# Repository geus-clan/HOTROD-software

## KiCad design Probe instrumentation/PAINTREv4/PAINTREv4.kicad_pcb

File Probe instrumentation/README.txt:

This folder contains the project files for the internal instrumentation of PAINTREv3.
The schematic and PCB layout (KiCad format), as well as gerber files for production, are included in the folder PAINTREv3.
The software for PAINTREv3 is included in the PAINTRE_V3XR folder. Various legacy versions featuring different methods are included, though the main PAINTRE_V3XR version is the recommended release, field-tested and confirmed functional.
Due to complications with the atmega328p processors used in assembly, our field versions of PAINTRE were retrofitted with Teensy-LC microprocessors. The connections to power and i2c lines are apparent in the setup of the software. Additional questions can be emailed to clan at geus.dk.

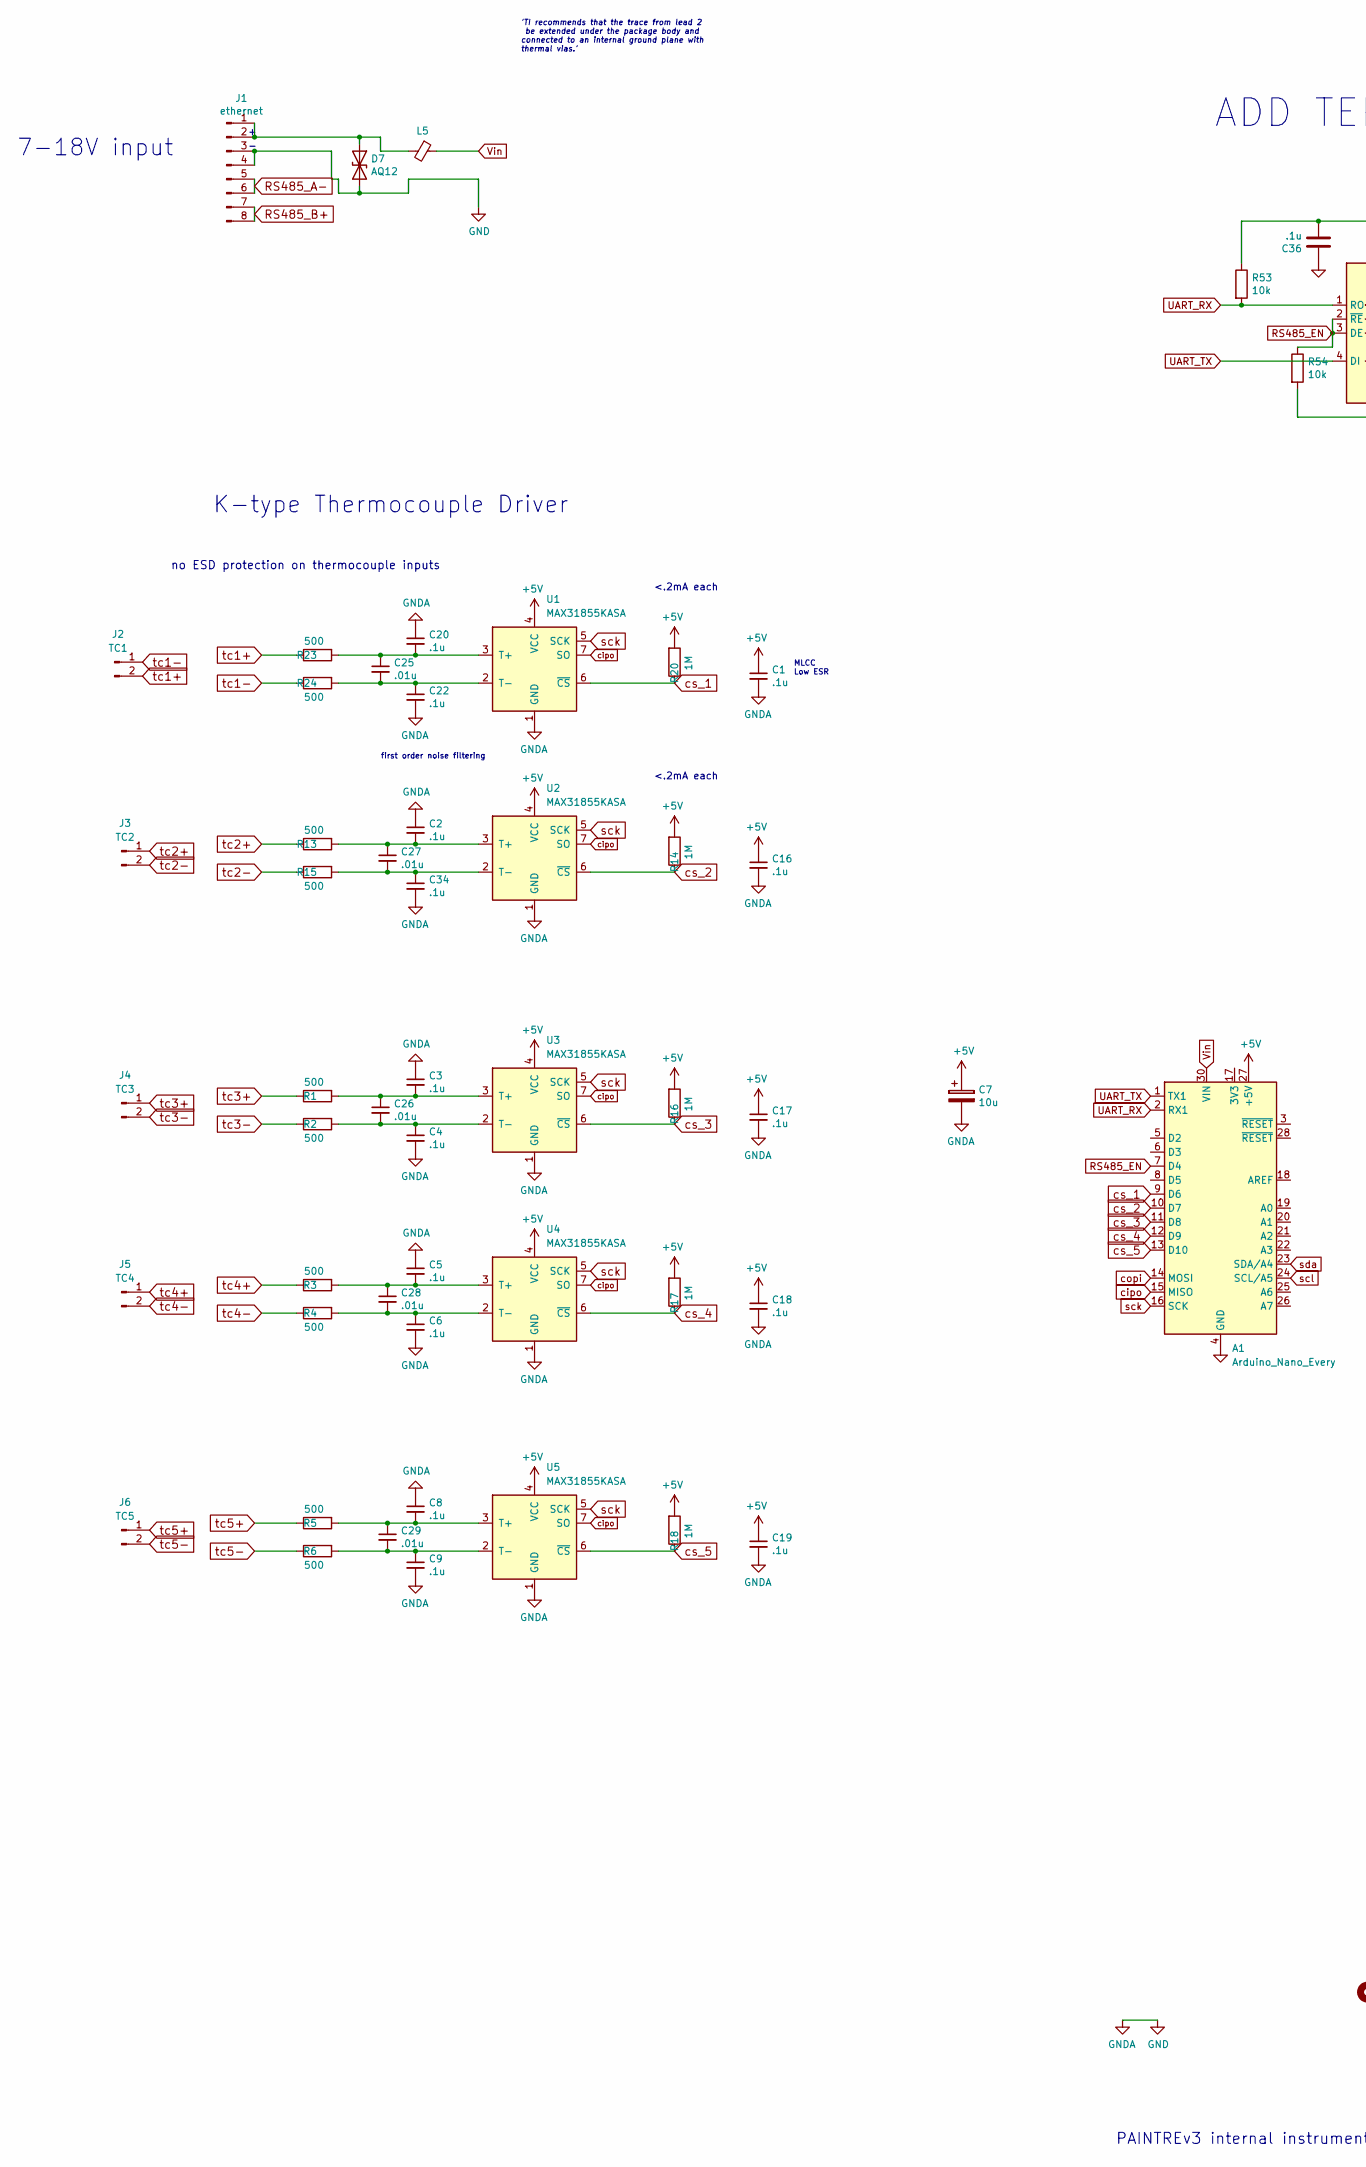
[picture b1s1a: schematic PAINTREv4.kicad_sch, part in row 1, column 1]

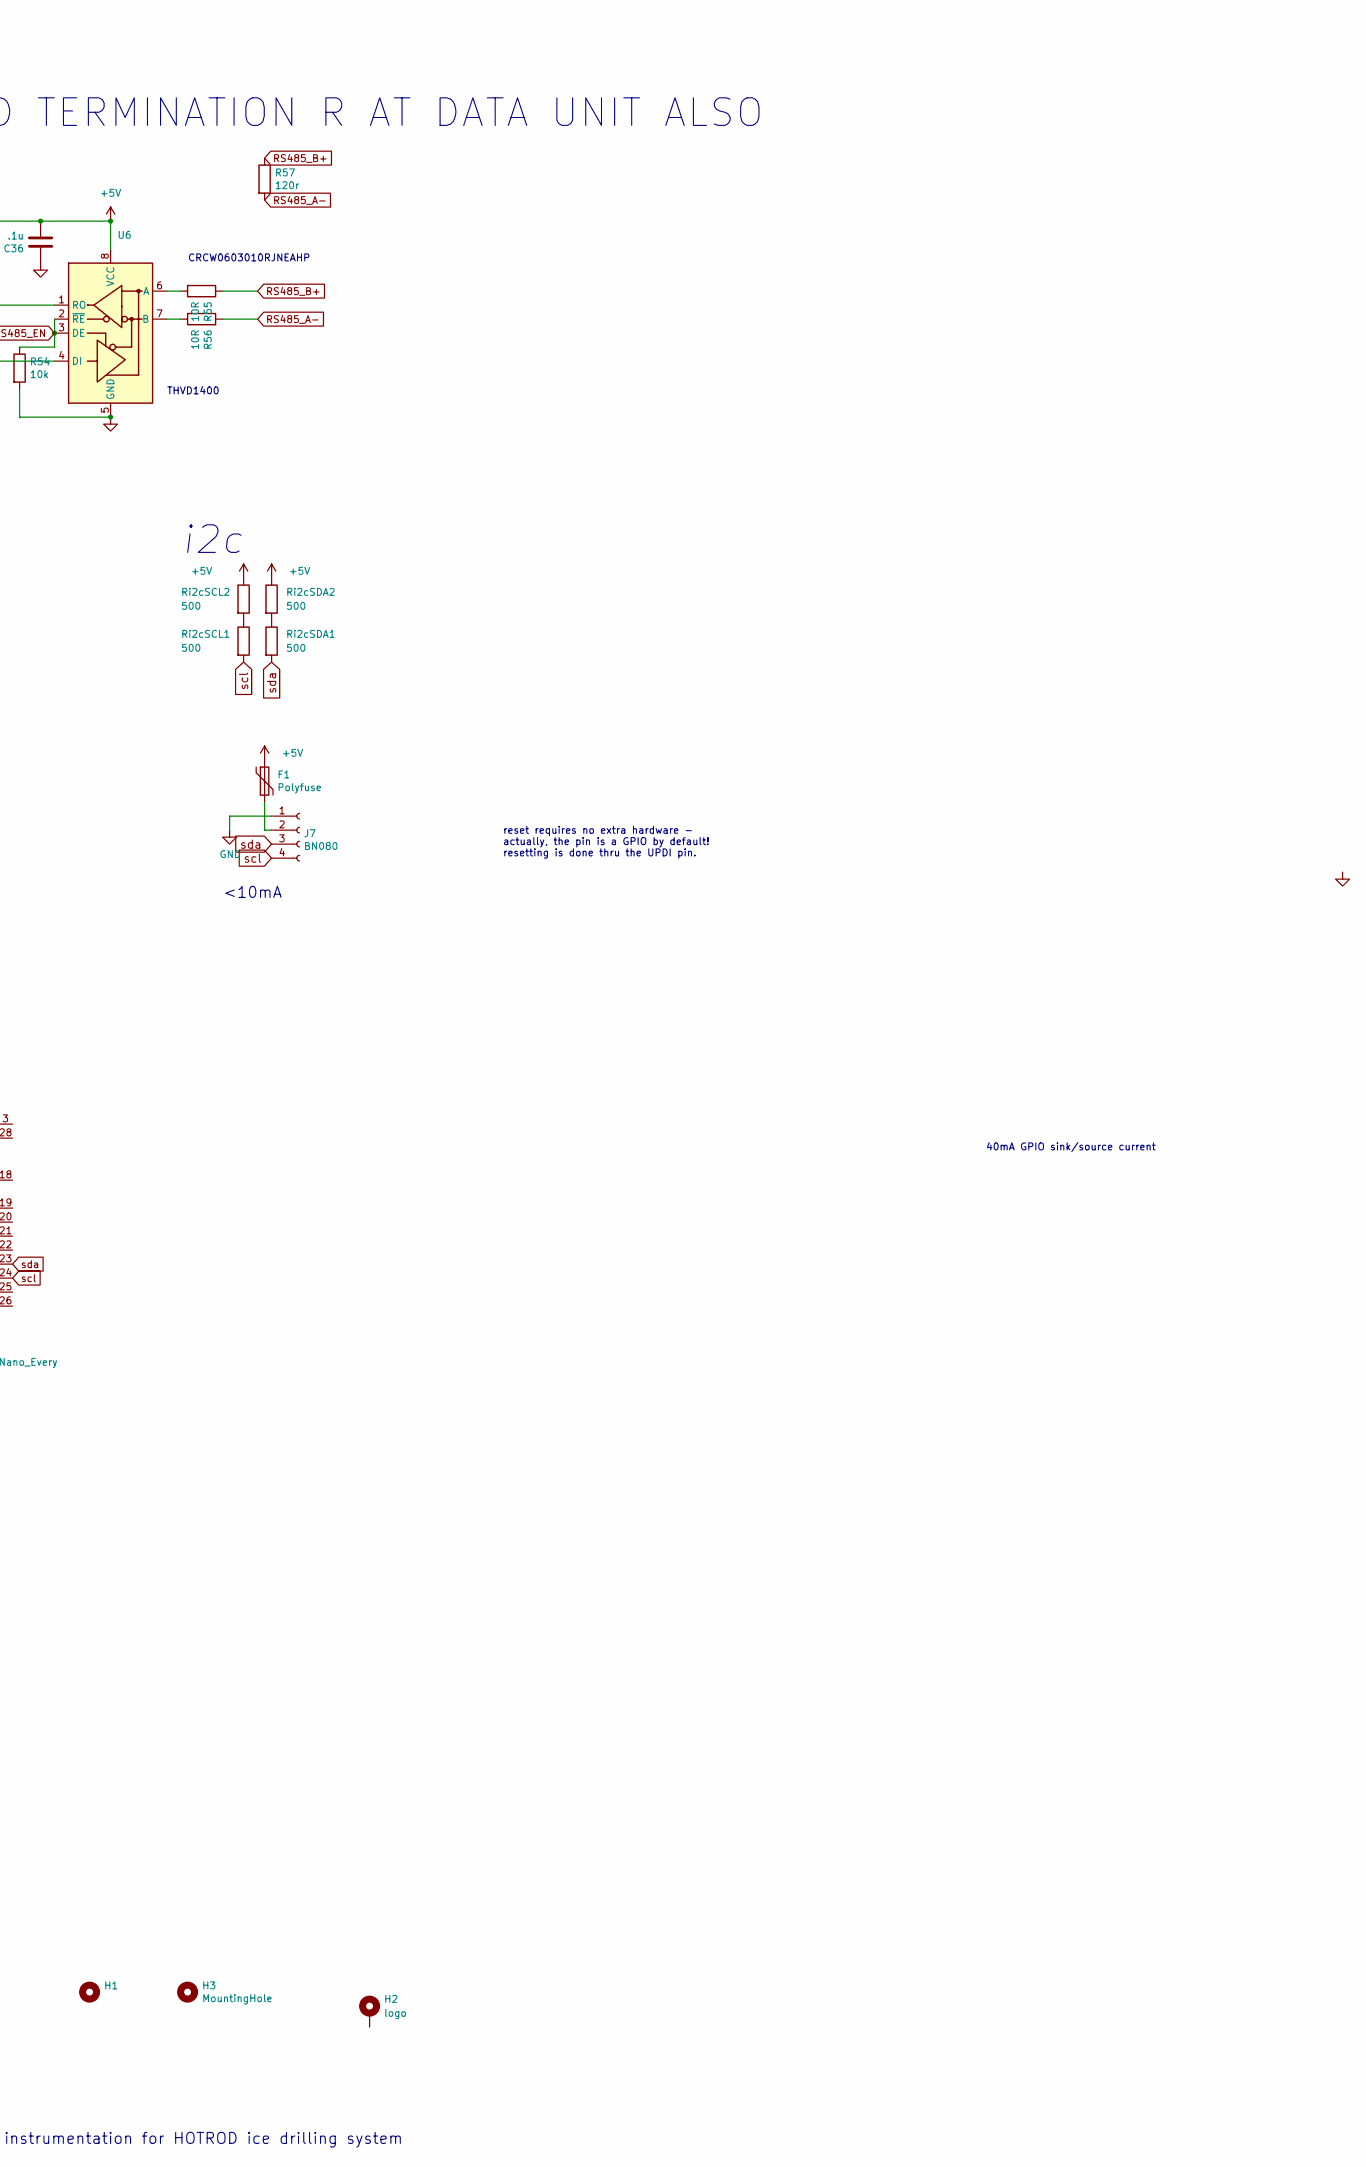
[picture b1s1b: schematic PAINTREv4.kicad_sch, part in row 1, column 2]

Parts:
A1: Arduino_Nano_Every; Arduino_Nano
C1, C2, C3, C4, C5, C6, C8, C9, C16, C17, C18, C19, C20, C22, C34: .1u; C_0603_1608Metric_fabdesignatorsmall
C7: 10u; C_1206_HandSoldering_silkscreenlabel
C25, C26, C27, C28, C29: .01u; C_0603_1608Metric_fabdesignatorsmall
C36: .1u; C_0603_1608Metric_fabdesignatorsmall; JLC part number C1525
D7: AQ12; SOT-23_handsoldering
F1: Polyfuse; Fuse_0603_1608Metric
H1: MountingHole_3.2mm_M3
H2: logo; paintre v4 logo
H3: MountingHole; MountingHole_3.2mm_M3
J1: ethernet; PinSocket_1x08_P2.00mm_Vertical
J2: TC1; PinSocket_1x02_P2.54mm_Vertical
J3: TC2; PinSocket_1x02_P2.54mm_Vertical
J4: TC3; PinSocket_1x02_P2.54mm_Vertical
J5: TC4; PinSocket_1x02_P2.54mm_Vertical
J6: TC5; PinSocket_1x02_P2.54mm_Vertical
J7: BN080; JST_SH_SM04B-SRSS-TB_04x1.00mm_Angled
L5: Ferrite_Bead_Small; ferrite_bead_1206
R1, R2, R3, R4, R5, R6, R13, R15, R23, R24: 500; R_0603_1608Metric_fabdesignatorsmall
R14, R16, R17, R18, R20: 1M; R_0603_1608Metric_fabdesignatorsmall
R53, R54: 10k; R_0603_1608Metric_fabdesignatorsmall; JLC part number C17903
R55, R56: 10R; R_0603_1608Metric_fabdesignatorsmall; JLC part number C17903
R57: 120r; R_1210_3225Metric_Pad1.30x2.65mm_HandSolder; JLC part number ---
Ri2cSCL1, Ri2cSCL2, Ri2cSDA1, Ri2cSDA2: 500; R_0603_1608Metric_fabdesignatorsmall
U1, U2, U3, U4, U5: MAX31855KASA; SOIC-8_3.9x4.9mm_P1.27mm
U6: SOT-5X3-8

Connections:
+5V: A1.27 (+5V), C1.1, C7.1, C16.1, C17.1, C18.1, C19.1, C36.2, F1.1, R14.2, R16.2, R17.2, R18.2, R20.2, R53.1, Ri2cSCL2.1, Ri2cSDA2.1, U1.4 (VCC), U2.4 (VCC), U3.4 (VCC), U4.4 (VCC), U5.4 (VCC), U6.8 (VCC)
unnamed: C2.2, C27.1, R13.2, U2.3 (T+)
unnamed: C20.2, C25.1, R23.2, U1.3 (T+)
unnamed: C22.1, C25.2, R24.2, U1.2 (T-)
unnamed: C3.2, C26.1, R1.2, U3.3 (T+)
unnamed: C4.1, C26.2, R2.2, U3.2 (T-)
unnamed: C27.2, C34.1, R15.2, U2.2 (T-)
unnamed: C5.2, C28.1, R3.2, U4.3 (T+)
unnamed: C6.1, C28.2, R4.2, U4.2 (T-)
unnamed: C8.2, C29.1, R5.2, U5.3 (T+)
unnamed: C9.1, C29.2, R6.2, U5.2 (T-)
unnamed: D7.1 (A1), J1.1, J1.2, L5.2
unnamed: F1.2, J7.2
unnamed: R55.2, U6.6 (A)
unnamed: R56.2, U6.7 (B)
unnamed: Ri2cSCL1.1, Ri2cSCL2.2
unnamed: Ri2cSDA1.1, Ri2cSDA2.2
RS485_A-: J1.5, J1.6, R56.1, R57.2
RS485_B+: J1.7, J1.8, R55.1, R57.1
RS485_EN: A1.7 (D4), R54.1, U6.2 (~RE), U6.3 (DE)
UART_RX: A1.2 (RX1), R53.2, U6.1 (RO)
UART_TX: A1.1 (TX1), U6.4 (DI)
Vin: A1.30 (VIN), L5.1
cipo: A1.15 (MISO), U1.7 (SO), U2.7 (SO), U3.7 (SO), U4.7 (SO), U5.7 (SO)
copi: A1.14 (MOSI)
cs_1: A1.9 (D6), R20.1, U1.6 (~CS)
cs_2: A1.10 (D7), R14.1, U2.6 (~CS)
cs_3: A1.11 (D8), R16.1, U3.6 (~CS)
cs_4: A1.12 (D9), R17.1, U4.6 (~CS)
cs_5: A1.13 (D10), R18.1, U5.6 (~CS)
sck: A1.16 (SCK), U1.5 (SCK), U2.5 (SCK), U3.5 (SCK), U4.5 (SCK), U5.5 (SCK)
scl: A1.24 (SCL/A5), J7.4, Ri2cSCL1.2
sda: A1.23 (SDA/A4), J7.3, Ri2cSDA1.2
tc1+: J2.2, R23.1
tc1-: J2.1, R24.1
tc2+: J3.1, R13.1
tc2-: J3.2, R15.1
tc3+: J4.1, R1.1
tc3-: J4.2, R2.1
tc4+: J5.1, R3.1
tc4-: J5.2, R4.1
tc5+: J6.1, R5.1
tc5-: J6.2, R6.1

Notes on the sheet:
<.2mA each
CRCW0603010RJNEAHP
MLCC Low ESR
first order noise filtering
reset requires no extra hardware - actually, the pin is a GPIO by default! resetting is done thru the UPDI pin.
THVD1400
40mA GPIO sink/source current
ADD TERMINATION R AT DATA UNIT ALSO
7-18V input
K-type Thermocouple Driver
PAINTREv3 internal instrumentation for HOTROD ice drilling system
<10mA
no ESD protection on thermocouple inputs
'TI recommends that the trace from lead 2 be extended under the package body and connected to an internal ground plane with thermal vias.'
i2c

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
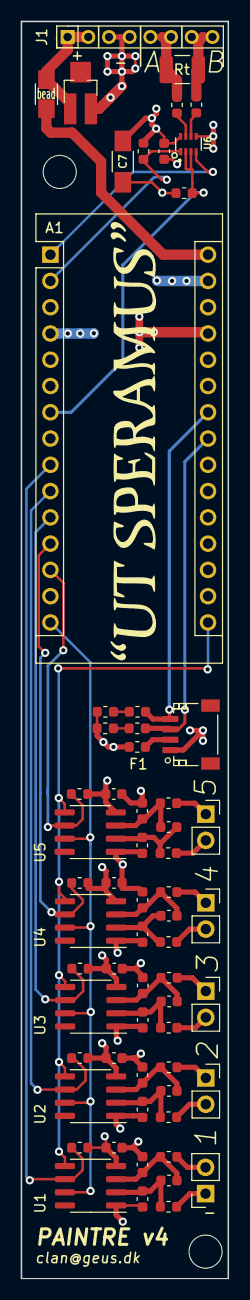
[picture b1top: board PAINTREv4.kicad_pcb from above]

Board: 4 copper layers, 20.0 x 121.5 mm, 66 parts (0 on the bottom side), 43 nets.

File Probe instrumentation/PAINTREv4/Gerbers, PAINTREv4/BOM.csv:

Designator,Package,Quantity,Value,JLC,SKU,MPN,LINK
"C1, C2, C3, C4, C5, C6, C8, C9, C16, C17, C18, C19, C20, C22, C34, C36",603,16,.1u,,302010139,CC0603KRX7R8BB105,
"C25, C26, C27, C28, C29",603,5,.01u,,302010138,CC0603KRX7R9BB104,
"R1, R2, R3, R4, R5, R6, R13, R15, R23, R24, Ri2cSCL1, Ri2cSCL2, Ri2cSDA1, Ri2cSDA2",603,14,500R,,301010157,RC0603JR-07510RL,
"R14, R16, R17, R18, R20",603,5,1M,,301010100,RC0603JR-071ML,
"R53, R54",603,2,10k,C25804,,,
"R55, R56",603,2,10R 330mW,,,CRCW060310R0JNEAHP,https://www.mouser.dk/ProductDetail/Vishay-Dale/CRCW060310R0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
F1,603,1,Polyfuse,,,0ZCM0002FF2G,https://www.mouser.dk/ProductDetail/Bel-Fuse/0ZCM0002FF2G/?q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
"U1, U2, U3, U4, U5",SOIC-8_3.9x4.9mm_P1.27mm,5,MAX31855KASA,,,MAX31855KASA+T,https://www.mouser.dk/ProductDetail/Maxim-Integrated/MAX3185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
U6,SOT-5X3-8,1,THVD1400,,,THVD1400DRLR,https://www.mouser.dk/ProductDetail/Texas-Instruments/THVD14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
D7,SOT-23,1,AQ12,,,,
J7,JST_SH_SM04B-SRSS-TB_04x1.00mm_Angled,1,BN080,,,PRT-14417,https://www.mouser.dk/ProductDetail/SparkFun/PRT-14417?qs=sG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

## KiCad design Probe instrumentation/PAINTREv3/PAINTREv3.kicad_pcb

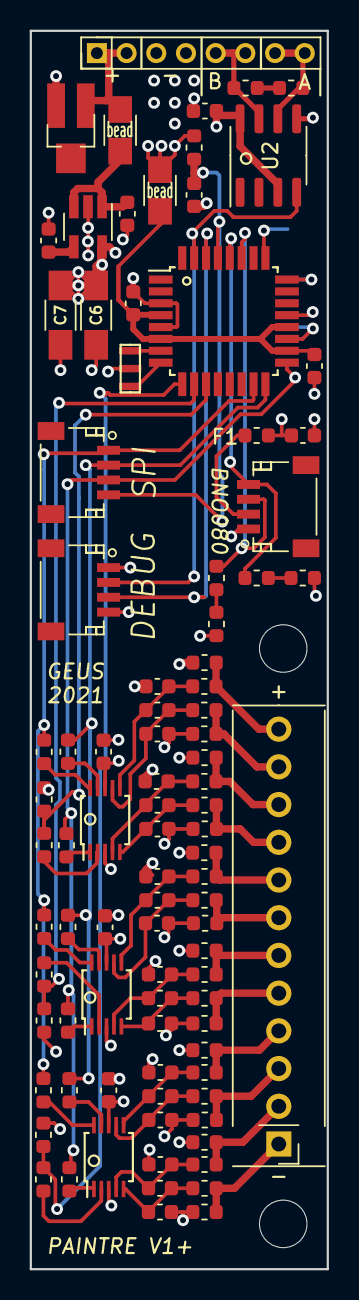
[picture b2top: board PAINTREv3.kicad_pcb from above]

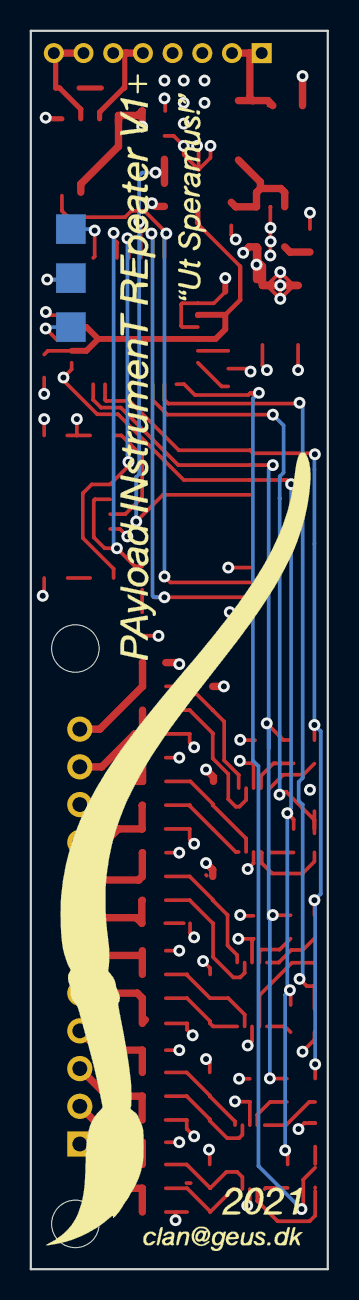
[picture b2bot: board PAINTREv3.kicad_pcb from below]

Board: 4 copper layers, 20.0 x 83.4 mm, 97 parts (3 on the bottom side), 64 nets.

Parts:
C1, C2, C4, C9, C11, C12, C14, C17, C18, C19, C20, C22, C23, C26, C27, C28, C29, C30: .1u; C_0603_1608Metric_fabdesignatorsmall
C3, C8, C10, C13, C15, C16, C21, C24, C25: 1u; C_0603_1608Metric_fabdesignatorsmall
C5: 10n; C_0603_1608Metric_fabdesignatorsmall
C6, C7: 10u; C_1206_HandSoldering_silkscreenlabel
D7: AQ12; SOT-23_handsoldering
F1: Polyfuse; Fuse_0603_1608Metric
H1, H2: MountingHole; MountingHole_3.2mm_M3
J1: ethernet; PinSocket_1x08_P2.00mm_Vertical
J2: SPI; JST_SH_SM04B-SRSS-TB_04x1.00mm_Angled
J3: TC; ScrewTerminal_1x12_P2.54mm_Vertical
J5: debug; JST_SH_SM04B-SRSS-TB_04x1.00mm_Angled
J7: BN080; JST_SH_SM04B-SRSS-TB_04x1.00mm_Angled
L5, L6: Ferrite_Bead_Small; ferrite_bead_1206
R1, R2, R3, R4, R12, R16, R20, R22, R25, R27, R28, R29, R30, R31, R40: 1M; R_0603_1608Metric_fabdesignatorsmall
R5, R6, R7, R8, R13, R15, R23, R24, R32, R33, R34, R35: 500; R_0603_1608Metric_fabdesignatorsmall
R9, R10, R11, R17, R18, R19, R21, R26, R36, R37, R38, R39: 50; R_0603_1608Metric_fabdesignatorsmall
R14: 4.7k; R_0603_1608Metric_fabdesignatorsmall
Ri2cSCL1, Ri2cSCL2, Ri2cSDA1, Ri2cSDA2: 500; R_0603_1608Metric_fabdesignatorsmall
Rterm1, Rterm2: 50; R_0603_1608Metric_fabdesignatorsmall
TP2: pc0; TestPoint_Pad_2.0x2.0mm
TP3: pc1; TestPoint_Pad_2.0x2.0mm
TP4: pc2; TestPoint_Pad_2.0x2.0mm
U1: LP2985-3.3; SOT-23-5_HandSoldering
U2: THVD1428DR; SOIC-8_3.9x4.9mm_P1.27mm
U3, U4, U7: ADS1118IDGS; TSSOP-10_3x3mm_P0.5mm
U5: ATmega328P-AU; TQFP-32_7x7mm_Pitch0.8mm
Y1: 8MHz Resonator; Resonator_SMD_muRata_CSTNE

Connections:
+3V3: C1.1, C6.1, C7.1, C9.1, C12.1, C23.1, C30.1, F1.1, J5.1, L6.1, R1.1, R3.1, R12.1, R14.1, R20.2, R22.1, R27.2, R28.1, R30.1, R40.2, Ri2cSCL2.1, Ri2cSDA2.1, U1.5, U2.3, U2.8, U3.8, U4.8, U7.8
GND: C1.2, C2.1, C4.2, C5.2, C6.2, C7.2, C9.2, C11.1, C12.2, C13.2, C14.2, C15.2, C16.2, C17.2, C18.1, C19.2, C20.1, C22.2, C23.2, C26.1, C27.2, C28.1, C29.2, C30.2, D7.2, J1.3, J1.4, J5.4, J7.1, R2.2, R4.2, R16.2, R25.2, R29.2, R31.2, U1.2, U2.5, U3.3, U4.3, U5.3, U5.5, U5.21, U7.3, Y1.2
unnamed: C2.2, C3.1, R13.2, U7.6
unnamed: C3.2, C4.1, R15.2, U7.7
unnamed: C5.1, U1.4
unnamed: C10.1, C18.2, R7.2, U3.6
unnamed: C10.2, C19.1, R8.2, U3.7
unnamed: C8.1, C11.2, R5.2, U3.4
unnamed: C13.1, C14.1, L6.2, U5.4, U5.6, U5.18, U5.20
unnamed: C16.1, L5.1, U1.1, U1.3
unnamed: C8.2, C17.1, R6.2, U3.5
unnamed: C20.2, C21.1, R23.2, U7.4
unnamed: C21.2, C22.1, R24.2, U7.5
unnamed: C24.1, C26.2, R32.2, U4.4
unnamed: C24.2, C27.1, R33.2, U4.5
unnamed: C25.1, C28.2, R34.2, U4.6
unnamed: C25.2, C29.1, R35.2, U4.7
unnamed: D7.1, J1.1, J1.2, L5.2
unnamed: F1.2, J7.2
unnamed: R9.1, U3.1
unnamed: R10.1, U3.10
unnamed: R11.1, U3.9
unnamed: R17.1, U7.1
unnamed: R18.1, U7.10
unnamed: R19.1, U7.9
unnamed: R21.1, U7.2
unnamed: R26.1, U3.2
unnamed: R36.1, U4.1
unnamed: R37.1, U4.10
unnamed: R38.1, U4.9
unnamed: R39.1, U4.2
unnamed: Ri2cSCL1.1, Ri2cSCL2.2
unnamed: Ri2cSDA1.1, Ri2cSDA2.2
unnamed: Rterm1.1, Rterm2.2
unnamed: TP2.1, U5.19
unnamed: TP3.1, U5.24
unnamed: TP4.1, U5.25
unnamed: U5.7, Y1.3
unnamed: U5.8, Y1.1
RS485-A: J1.7, J1.8, Rterm2.1, U2.6
RS485-B: J1.5, J1.6, Rterm1.2, U2.7
cs_1: R20.1, R21.2, U5.9
cs_2: R26.2, R27.1, U5.10
cs_3: R39.2, R40.1, U5.11
miso: J2.2, R11.2, R19.2, R38.2, U5.16
mosi: J2.1, R10.2, R18.2, R37.2, U5.15
reset: C15.1, J2.4, R14.2, U5.29
rxd: J5.3, U5.30
sck: J2.3, R9.2, R17.2, R36.2, U5.17
scl: J7.4, Ri2cSCL1.2, U5.28
sda: J7.3, Ri2cSDA1.2, U5.27
tc1+: J3.2, R22.2, R23.1
tc1-: J3.1, R24.1, R25.1
tc2+: J3.4, R12.2, R13.1
tc2-: J3.3, R15.1, R16.1
tc3+: J3.6, R1.2, R5.1
tc3-: J3.5, R2.1, R6.1
tc4+: J3.8, R3.2, R7.1
tc4-: J3.7, R4.1, R8.1
tc5+: J3.10, R28.2, R32.1
tc5-: J3.9, R29.1, R33.1
tc6+: J3.12, R30.2, R34.1
tc6-: J3.11, R31.1, R35.1
txd: J5.2, U2.4, U5.31

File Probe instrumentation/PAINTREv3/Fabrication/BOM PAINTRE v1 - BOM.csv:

Designator,Package,Quantity,Value,,SKU,MPL,LINK
C3;C25;C24;C21;C16;C15;C13;C10;C8,C_0603,9,1u,,302010139,CC0603KRX7R8BB105,
C4;C2;C1;C30;C29;C28;C27;C26;C23;C22;C20;C19;C18;C17;C14;C12;C11;C9,C_0603,18,.1u,,302010138,CC0603KRX7R9BB104,
C5,C_0603,1,10n,,302010140,CC0603KRX7R9BB103,
C7;C6,C_1206,2,10u,,302010181,CC1206KKX5R8BB106,
D7,SOT-23,1,AQ12,,,AQ12-02HTG,https://www.mouser.dk/ProductDetail/Littelfuse/AQ12-02HTG?qs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
,,,,,,,
J2; J5; J7,JST_SH_SM04B-SRSS-TB_04x1.00mm_Angled,3,SPI; debug; BN080,,,PRT-14417,https://www.mouser.dk/ProductDetail/SparkFun/PRT-14417?qs=sG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
R14,R_0603,1,4.7k,,301010195,RC0603FR-074K7L,
Ri2cSDA2;Ri2cSCL2;Ri2cSDA1;Ri2cSCL1;R35;R34;R33;R32;R24;R23;R15;R13;R8;R7;R6;R5,R_0603_1608Metric_fabdesignatorsmall,16,500,,301010157,RC0603JR-07510RL,
Rterm2;Rterm1;R39;R38;R37;R36;R26;R21;R19;R18;R17;R11;R10;R9,R_0603,14,50,,301010225,RC0603FR-0751RL,
R40;R31;R30;R29;R28;R27;R25;R22;R20;R16;R12;R4;R3;R2;R1,R_0603,15,1M,,301010100,RC0603JR-071ML,
,,,,,,,
U1,SOT-23-5_HandSoldering,1,LP2985-3.3,,,LP2985AIM5-3.3/NOPB,https://www.mouser.dk/ProductDetail/Texas-Instruments/LP2985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
U2,SOIC-8_3.9x4.9mm_P1.27mm,1,THVD1428DR,,,THVD1428DR,https://www.mouser.dk/ProductDetail/Texas-Instruments/THVD14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
U4;U3;U7,TSSOP-10_3x3mm_P0.5mm,3,"ADS1118IDGS
",,,ADS1118IDGSR,https://www.mouser.dk/ProductDetail/Texas-Instruments/ADS111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
U5,TQFP-32_7x7mm_Pitch0.8mm,1,ATmega328P-AU,,310010049,ATMEGA328P-AU,https://www.mouser.dk/ProductDetail/Microchip-Technology-Atm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
Y1,Resonator_SMD_muRata_CSTNE,1,8MHz Resonator,,,CSTNE8M00GH5C000R0,https://www.mouser.dk/ProductDetail/81-CSTNE8M00GH5C000R
,,,,,,,
F1,Fuse_0603,1,Polyfuse,,,0ZCM0002FF2G,https://www.mouser.dk/ProductDetail/Bel-Fuse/0ZCM0002FF2G/?q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
,,,,,,,
L5;L6,ferrite_bead_handsolder-1206,2,Ferrite_Bead_Small,,(or similar),2512061527Y0,https://www.mouser.dk/ProductDetail/Fair-Rite/2512061527Y0/?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

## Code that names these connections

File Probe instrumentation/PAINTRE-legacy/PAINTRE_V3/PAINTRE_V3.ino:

/**
 * PAINTREsoft V3 ----- Chris Shields, 2022, clan@geus.dk
 * CC-BY-SA
 * 
 * Reads three on-board ADS1118 ADCs configured for reading K-type thermocouples embedded in heating cartridges
 * Polls an external KX132 breakout board (SparkFun)
 * Builds and transmits a string back to mission control.
 * 
 * Contact for further details.
 * 
 * Most code for interfacing KX13x and ADS1118 adapted from their respective library examples and datasheets. Many thanks to the authors.
 * 
 */

#include "ADS1118.h"
#include <SPI.h>
#include <Wire.h>
#include <ReclaimerLabs_Thermocouple.h>
#include <elapsedMillis.h>
#include "SparkFun_Qwiic_KX13X.h"

#define CS_1 A1
#define CS_2 A2
#define CS_3 A3

ADS1118 a3(CS_3);
ADS1118 a2(CS_2);
ADS1118 a1(CS_1);

QwiicKX132 kxAccel;

outputData IMUData; // This will hold the accelerometer's output. 
double roll = 0.00, pitch = 0.00;       //Roll & Pitch are the angles which rotate by the axis X and y


void setup(){
    Serial.begin(9600);
    Serial1.begin(9600);
    
  Wire.begin();
  if( !kxAccel.begin() ){
    Serial.println("KX132 offline");
  }

  if( !kxAccel.initialize(DEFAULT_SETTINGS)){ // Loading default settings.
    Serial.println("Could not initialize the IMU.");
  }
  else
    Serial.println("IMU ready.");  

  a3.begin();
  a2.begin(); //Initialize the ADS1118. Default setting: PULLUP RESISTOR, ADC MODE, RATE 8SPS, SINGLE SHOT, ±0.256V, DIFFERENTIAL AIN0-AIN1
  a1.begin();
    
    digitalWrite(CS_1, LOW); //Logic low on all ADS1118 chip select pins on startup
    digitalWrite(CS_2, LOW);
    digitalWrite(CS_3, LOW);

 
    a1.setSamplingRate(a2.RATE_8SPS);             //Using the setter method to change the sampling rate
    a1.setContinuousMode();                            //Using the setter method to set it to continuous mode
    a1.enablePullup();                                 //Using the setter method to enable the pull-up resistor in Dout
    
    a2.setSamplingRate(a2.RATE_8SPS);             //Using the setter method to change the sampling rate
    a2.setContinuousMode();                            //Using the setter method to set it to continuous mode
    a2.enablePullup();                                 //Using the setter method to enable the pull-up resistor in Dout

    a3.setSamplingRate(a2.RATE_8SPS);             //Using the setter method to change the sampling rate
    a3.setContinuousMode();                            //Using the setter method to set it to continuous mode
    a3.enablePullup();  
    
  Serial.print("TC setup complete.");

}


void loop(){      //output format: t1,2,3,4,5,6, int1,2,3, x,y,z, pitch,roll
 Serial.print("/*"); //frame start
 returnTemp();
 readIMU();
 Serial.print("*/"); //frame end
 Serial.println();
}

void returnTemp(){
   digitalWrite(CS_1,LOW);
   digitalWrite(CS_2,LOW);
   digitalWrite(CS_3,LOW);

   double iT1, iT2, iT3;
   iT1 = a1.getTemperature(); //find cold junction temps (needed for TC calculations)
   iT2 = a2.getTemperature();
   iT3 = a3.getTemperature();


    readTC(a3.getMilliVolts(a3.DIFF_0_1),iT3);
    readTC(a3.getMilliVolts(a3.DIFF_2_3),iT3);
    readTC(a2.getMilliVolts(a2.DIFF_0_1),iT2);
    readTC(a2.getMilliVolts(a2.DIFF_2_3),iT2);
    readTC(a1.getMilliVolts(a1.DIFF_0_1),iT1);
    readTC(a1.getMilliVolts(a1.DIFF_2_3),iT1);
  
Serial.print("\t");

   Serial.print(iT1);   Serial.print(", "); //print internal temperatures
   Serial.print(iT2);   Serial.print(", ");
   Serial.print(iT3);   Serial.print(", ");  
   
   Serial.print("\t");
 
}

void readTC(double diff_volt_mV, double cold_junc_C){
  double hot_junc_C;
  int32_t return_val;
  
  return_val = ReclaimerLabs_Thermocouple::calc_temp(TYPE_K, diff_volt_mV, cold_junc_C, &hot_junc_C);
  Serial.print(hot_junc_C);
  Serial.print(",");
}

void readIMU(){

  double x_Buff = float(IMUData.xData);
  double y_Buff = float(IMUData.yData);
  double z_Buff = float(IMUData.zData);
  
  IMUData = kxAccel.getAccelData(); 
  
  Serial.print(IMUData.xData, 4); Serial.print(", "); //acceleration X
  Serial.print(IMUData.yData, 4); Serial.print(", "); //acceleration Y
  Serial.print(IMUData.zData, 4); Serial.print(", "); //acceleration Z

  roll = atan2(y_Buff , z_Buff) * 57.3;
  pitch = atan2((- x_Buff) , sqrt(y_Buff * y_Buff + z_Buff * z_Buff)) * 57.3;
  Serial.print(roll); Serial.print(", ");
  Serial.print(pitch);
}

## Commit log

2022-03-30 add update
2022-08-29 should have been added pre-trip
2022-08-29 update directory
2022-08-29 add PCB
2022-08-29 readme
2022-08-29 add machining files
2022-08-31 update pre-arduino
2022-08-31 arduino version
2022-09-02 V4 PCB redesign (max ICs)
2022-09-02 v4 pcb updates
